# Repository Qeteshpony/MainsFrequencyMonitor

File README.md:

# Mains Frequency Monitor

**Part of the board has mains voltage on it so it is dangerous to handle the board outside of a proper case while powered! It lies in your own responsibility to use proper safety precautions when working on this project!**

[Hardware Documentation](https://qeteshpony.github.io/MainsFrequencyMonitor)

Single board solution to power an ESP32 and use it to measure the mains frequency through an optoisolator

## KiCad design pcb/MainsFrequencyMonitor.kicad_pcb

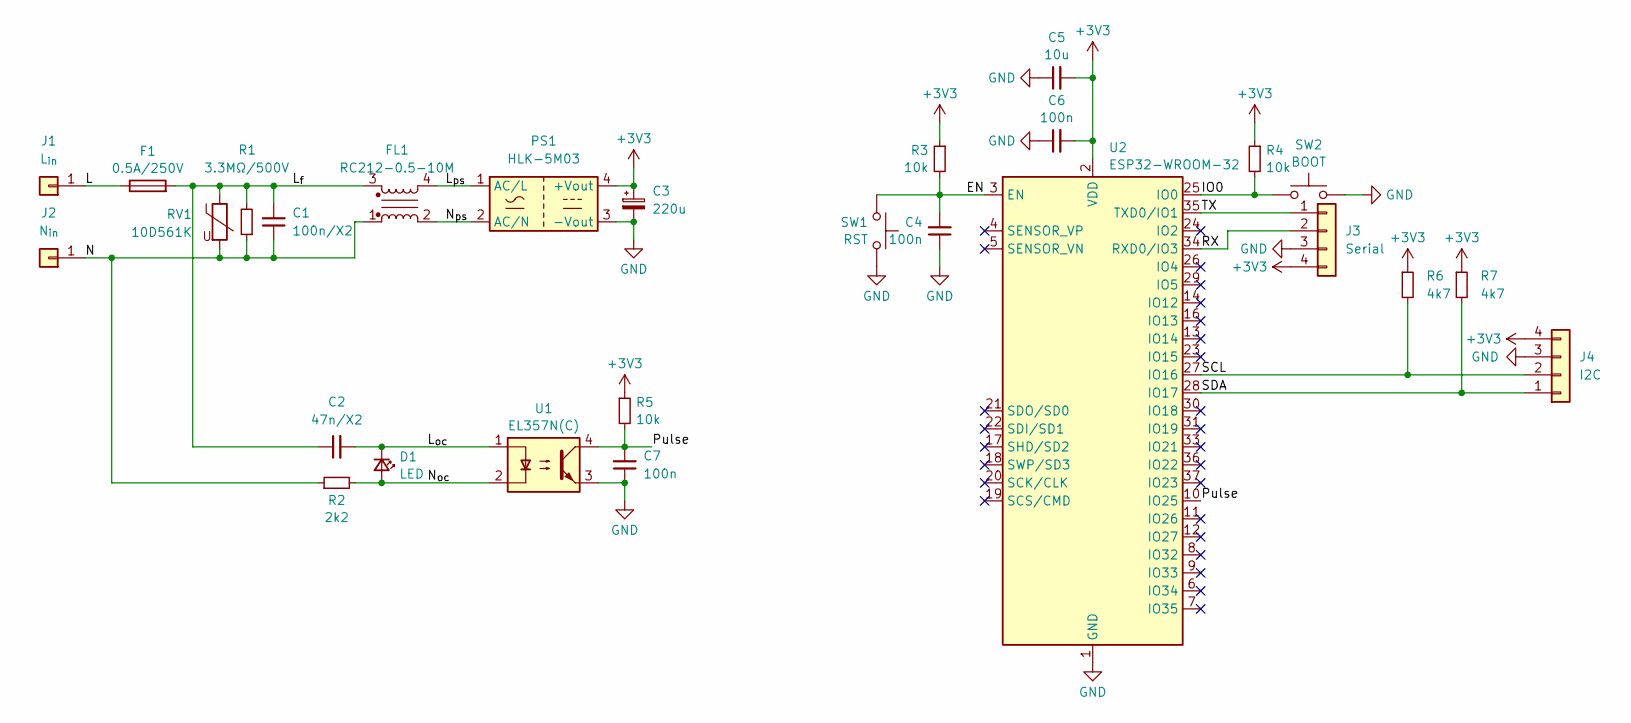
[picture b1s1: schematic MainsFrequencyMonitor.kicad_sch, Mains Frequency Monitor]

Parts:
C1: 100n/X2; C_Rect_L13.0mm_W5.0mm_P10.00mm_FKS3_FKP3_MKS4
C2: 47n/X2; C_Rect_L10.3mm_W5.7mm_P7.50mm_MKS4
C3: 220u; CP_Radial_D6.3mm_P2.50mm
C4, C6, C7: 100n; C_0603_1608Metric_Pad1.08x0.95mm_HandSolder; LCSC C14663
C5: 10u; C_0603_1608Metric_Pad1.08x0.95mm_HandSolder; LCSC C19702
D1: LED; LED_0805_2012Metric_Pad1.15x1.40mm_HandSolder; LCSC C84256
F1: 0.5A/250V; Fuseholder_TR5_Littelfuse_No560_No460
FL1: RC212-0.5-10M; Schaffner_RC212
J1: L_{in}; SolderWire-0.75sqmm_1x01_D1.25mm_OD3.5mm
J2: N_{in}; SolderWire-0.75sqmm_1x01_D1.25mm_OD3.5mm
J3: Serial; PinSocket_1x04_P2.54mm_Vertical
J4: I2C; JST_PH_B4B-PH-K_1x04_P2.00mm_Vertical; LCSC C157926
PS1: HLK-5M03; Converter_ACDC_Hi-Link_HLK-5Mxx
R1: 3.3MΩ/500V; R_Axial_DIN0207_L6.3mm_D2.5mm_P7.62mm_Horizontal
R2: 2k2; R_Axial_DIN0207_L6.3mm_D2.5mm_P7.62mm_Horizontal
R3, R4, R5: 10k; R_0603_1608Metric_Pad0.98x0.95mm_HandSolder; LCSC C25804
R6, R7: 4k7; R_0603_1608Metric_Pad0.98x0.95mm_HandSolder; LCSC C23162
RV1: 10D561K; RV_Disc_D12mm_W5.8mm_P7.5mm
SW1: RST; SW_Push_1P1T_XKB_TS-1187A; LCSC C318884
SW2: BOOT; SW_Push_1P1T_XKB_TS-1187A; LCSC C318884
U1: EL357N(C); SO-4_4.4x3.6mm_P2.54mm; LCSC C29981
U2: ESP32-WROOM-32; LCSC C503588

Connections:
+3V3: C3.1, C5.2, C6.2, J3.4, J4.4, PS1.4 (+Vout), R3.1, R4.1, R5.1, R6.1, R7.1, U2.2 (VDD)
/EN: C4.2, R3.2, SW1.2, U2.3 (EN)
/IO0: R4.2, SW2.1, U2.25 (IO0)
/L: F1.1, J1.1
/L_{f}: C1.2, C2.1, F1.2, FL1.3, R1.2, RV1.1
/L_{oc}: C2.2, D1.1 (K), U1.1
/L_{ps}: FL1.4, PS1.1 (AC/L)
/N: C1.1, FL1.1, J2.1, R1.1, R2.1, RV1.2
/N_{oc}: D1.2 (A), R2.2, U1.2
/N_{ps}: FL1.2, PS1.2 (AC/N)
/Pulse: C7.2, R5.2, U1.4, U2.10 (IO25)
/RX: J3.2, U2.34 (RXD0/IO3)
/SCL: J4.2, R6.2, U2.27 (IO16)
/SDA: J4.1, R7.2, U2.28 (IO17)
/TX: J3.1, U2.35 (TXD0/IO1)
GND: C3.2, C4.1, C5.1, C6.1, C7.1, J3.3, J4.3, PS1.3 (-Vout), SW1.1, SW2.2, U1.3, U2.1 (GND), U2.15 (GND), U2.38 (GND), U2.39 (GND)

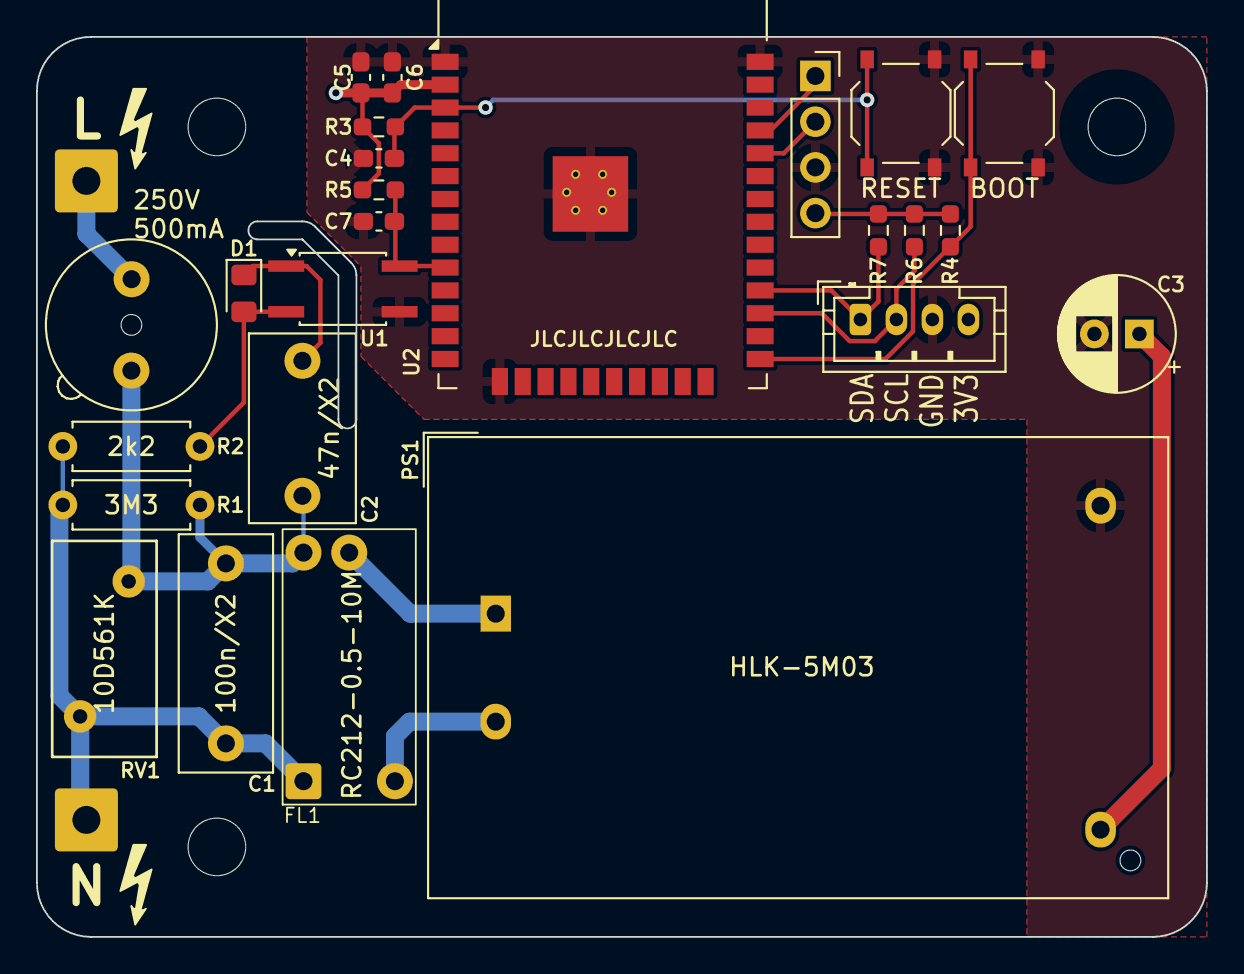
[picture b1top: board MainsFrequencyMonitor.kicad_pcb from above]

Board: 2 copper layers, 65.0 x 50.0 mm, 27 parts (0 on the bottom side), 16 nets.

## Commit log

2024-05-26 feat: initial commit
2024-05-26 chore(main): release 1.0.0
2024-05-26 chore: re-release after fixing config
    Release-As: 1.0.0
2024-06-15 chore: re-release after fixing config
2024-06-15 fix: add capacitor to optocouplers output
    Output of the optocoupler was not a smooth square wave form but had some voltage spikes. Adding a 100nF capacitor to the output solved this.
2024-06-15 git: add kicad lock files to gitignore
2024-06-15 chore(main): release 1.0.1
2024-08-29 ci: remove dependency between jobs
